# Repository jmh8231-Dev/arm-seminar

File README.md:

# ARM Seminar Board — Training Kit Rev 2.0

> **MCU:** STM32F405VGT6 (Cortex‑M4)  

ARM Seminar Board (Rev 2.0)는 GPIO부터 SDIO, FMC‑SDRAM, QSPI, CAN, USB, Wi‑Fi(IoT), RTC까지  
현업에서 자주 쓰는 주변장치를 **한 장의 보드에서 단계적으로 실습**할 수 있도록 구성한 트레이닝 키트입니다.

---

## Contents
- [Hardware overview](#hardware-overview)
- [Images](#images)
- [Getting started](#getting-started)
- [Peripheral quick map](#peripheral-quick-map)
- [Curriculum (16 + n)](#curriculum-16--n)
- [Revision notes](#revision-notes)
- [Repository layout](#repository-layout)
- [License](#license)

---

## Hardware overview

> 아래 구성은 **블록 다이어그램 / 보드 실크 라벨 기준**으로 정리했습니다.

### Core / Storage

| Category | Item | Interface / Notes |
|---|---|---|
| MCU | STM32F405VGT6 | Cortex‑M4 |
| microSD | microSD socket | **SDIO (4‑bit)** |

### USB / Debug

| Item | Notes |
|---|---|
| USB Type‑C | 5V 전원 / PC 연결 |
| USB OTG FS | USB 2.0 Full‑Speed |
| UART‑to‑USB | FT232RL 기반 로그/콘솔 |

### Display

| Item | Notes |
|---|---|
| 2004 CLCD | 캐릭터 LCD |

### Connectivity

| Item | Interface / Notes |
|---|---|
| Wi‑Fi module | ESP‑12F (**UART**) |
| CAN | CAN Tx/Rx + 커넥터 |

### Sensors / Inputs / Actuators

| Item | Notes |
|---|---|
| RTC | DS3231 + CR2032 |
| EEPROM | I2C |
| Temp sensor | AS6221 |
| Analog inputs | CDS Cell, 가변저항(ADC 실습) |
| User I/O | LEDs, Buttons, GPIO/EXTI 스위치 |
| Actuator | SG90 Servo(PWM), Passive Buzzer |

---

## Images

### Block diagram

### Board photos

---

## Getting started

### Power
- **USB Type‑C**로 5V 전원 공급 (PC/어댑터 모두 가능)
- RTC는 **CR2032** 장착 시 전원 분리 후에도 시간 유지

### Flash / Debug
- **ST‑Link/V2 헤더**로 다운로드/디버깅
- 또는 UART‑to‑USB(FT232RL)로 시리얼 콘솔/로그 출력

### Recommended dev environment
- STM32CubeIDE, STM32CubeMX (권장)
- (선택) STM32CubeProgrammer, Logic Analyzer, CAN‑USB, USB‑TTL

---

## Peripheral quick map

교육 진행 시 “오늘 실습 대상”을 빠르게 체크할 수 있도록 묶었습니다.

- **GPIO / EXTI:** 버튼/스위치, LED  
- **ADC / DMA:** CDS Cell, 가변저항  
- **Timer / PWM:** Servo(SG90), Buzzer  
- **UART:** PC 디버그 콘솔, Wi‑Fi(ESP‑12F)  
- **I2C:** EEPROM, AS6221, DS3231(RTC)  
- **SPI:** 확장(예: VS1003 등)  
- **SDIO / FATFS:** microSD 파일 시스템  
- **CAN:** 보드 커넥터  

---

## Curriculum (10 + 6)

세미나는 총 **10 + 6회차**로 구성되며, 초급 → 고급으로 난이도가 점진적으로 상승하도록 설계했습니다.

- CubeIDE / GPIO / EXTI
- UART(폴링/인터럽트), printf 디버그
- CLCD 출력, ADC/DMA, Timer
- PWM/서보/버저 제어
- USB (예: Mass Storage)
- SDIO + FATFS, SPI, I2C, CAN
- FreeRTOS

---

## Revision notes

Rev 1.0 대비 주요 변경 사항 (요약)

- RTC 배터리 홀더 위치 변경(Back side)
- USB Type‑C 라인 다이오드 삭제
- UART 기반 업로드/연동 편의 개선
- 실크스크린 영역/사이즈 조정, 날짜/버전 업데이트

---

## License

**All Rights Reserved.**

본 저장소의 회로/PCB/문서/이미지/콘텐츠는 저작권자의 사전 서면 허가 없이  
**복제, 배포, 상업적 이용, 2차 저작물 제작**을 금지합니다.

교육/연구 목적의 검토가 필요하다면 저작권자에게 사용 허가를 요청해 주세요.  
자세한 내용은 `LICENSE`를 참조합니다.

© 2025 MyungHoon Jung. All rights reserved.

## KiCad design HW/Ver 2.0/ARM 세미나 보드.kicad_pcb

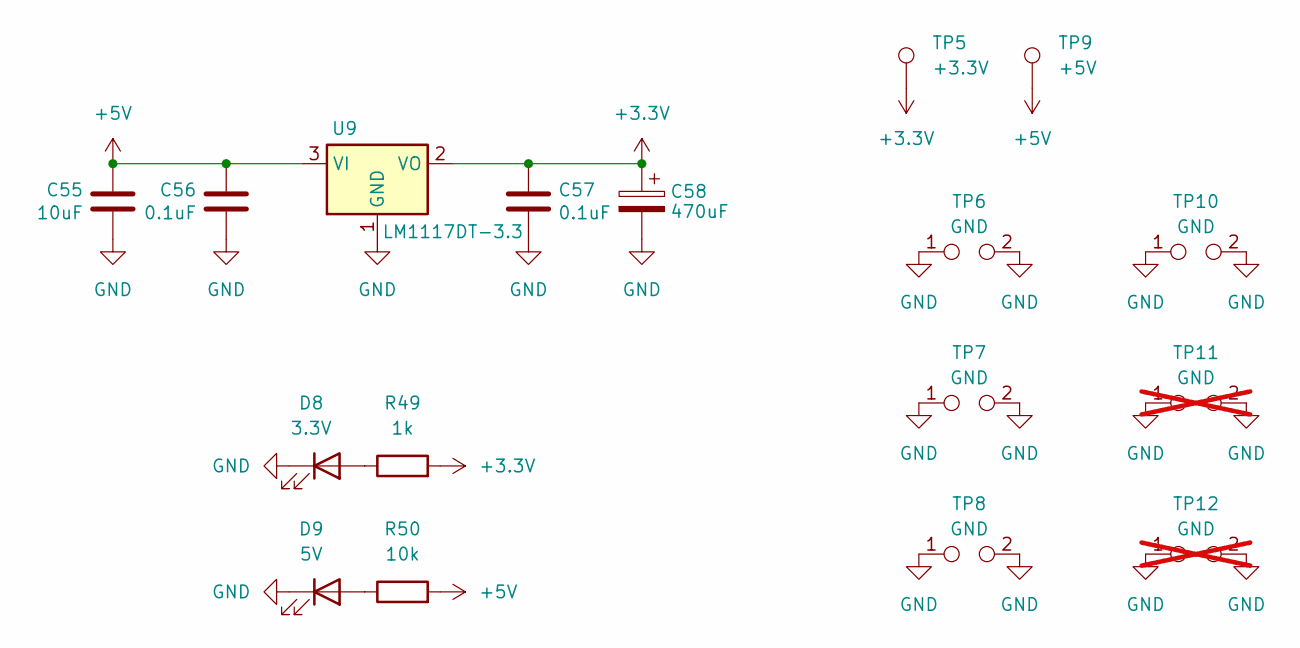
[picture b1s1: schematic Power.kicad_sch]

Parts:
C55: 10uF; C_1206_3216Metric
C56, C57: 0.1uF; C_0805_2012Metric
C58: 470uF; MVG25WV470M
D8: 3.3V; LED_0805_2012Metric
D9: 5V; LED_0805_2012Metric
R49: 1k; R_0805_2012Metric
R50: 10k; R_0805_2012Metric
TP5: +3.3V; TestPoint_Pad_D1.5mm
TP6, TP7, TP8, TP10: GND; TestPoint_2Pads_Pitch5.08mm_Drill1.3mm
TP9: +5V; TestPoint_Pad_D1.5mm
TP11, TP12: GND; TestPoint_2Pads_Pitch5.08mm_Drill1.3mm; not fitted
U9: LM1117DT-3.3; TO-252-3_TabPin2

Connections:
+3.3V: C57.2, C58.1, R49.2, TP5.1, U9.2 (VO); also elsewhere on the board
+5V: C55.2, C56.2, R50.2, TP9.1, U9.3 (VI); also elsewhere on the board
GND: C55.1, C56.1, C57.1, C58.2, D8.1 (K), D9.1 (K), TP6.1, TP6.2, TP7.1, TP7.2, TP8.1, TP8.2, TP10.1, TP10.2, TP11.1, TP11.2, TP12.1, TP12.2, U9.1 (GND); also elsewhere on the board
unnamed: D8.2 (A), R49.1
unnamed: D9.2 (A), R50.1

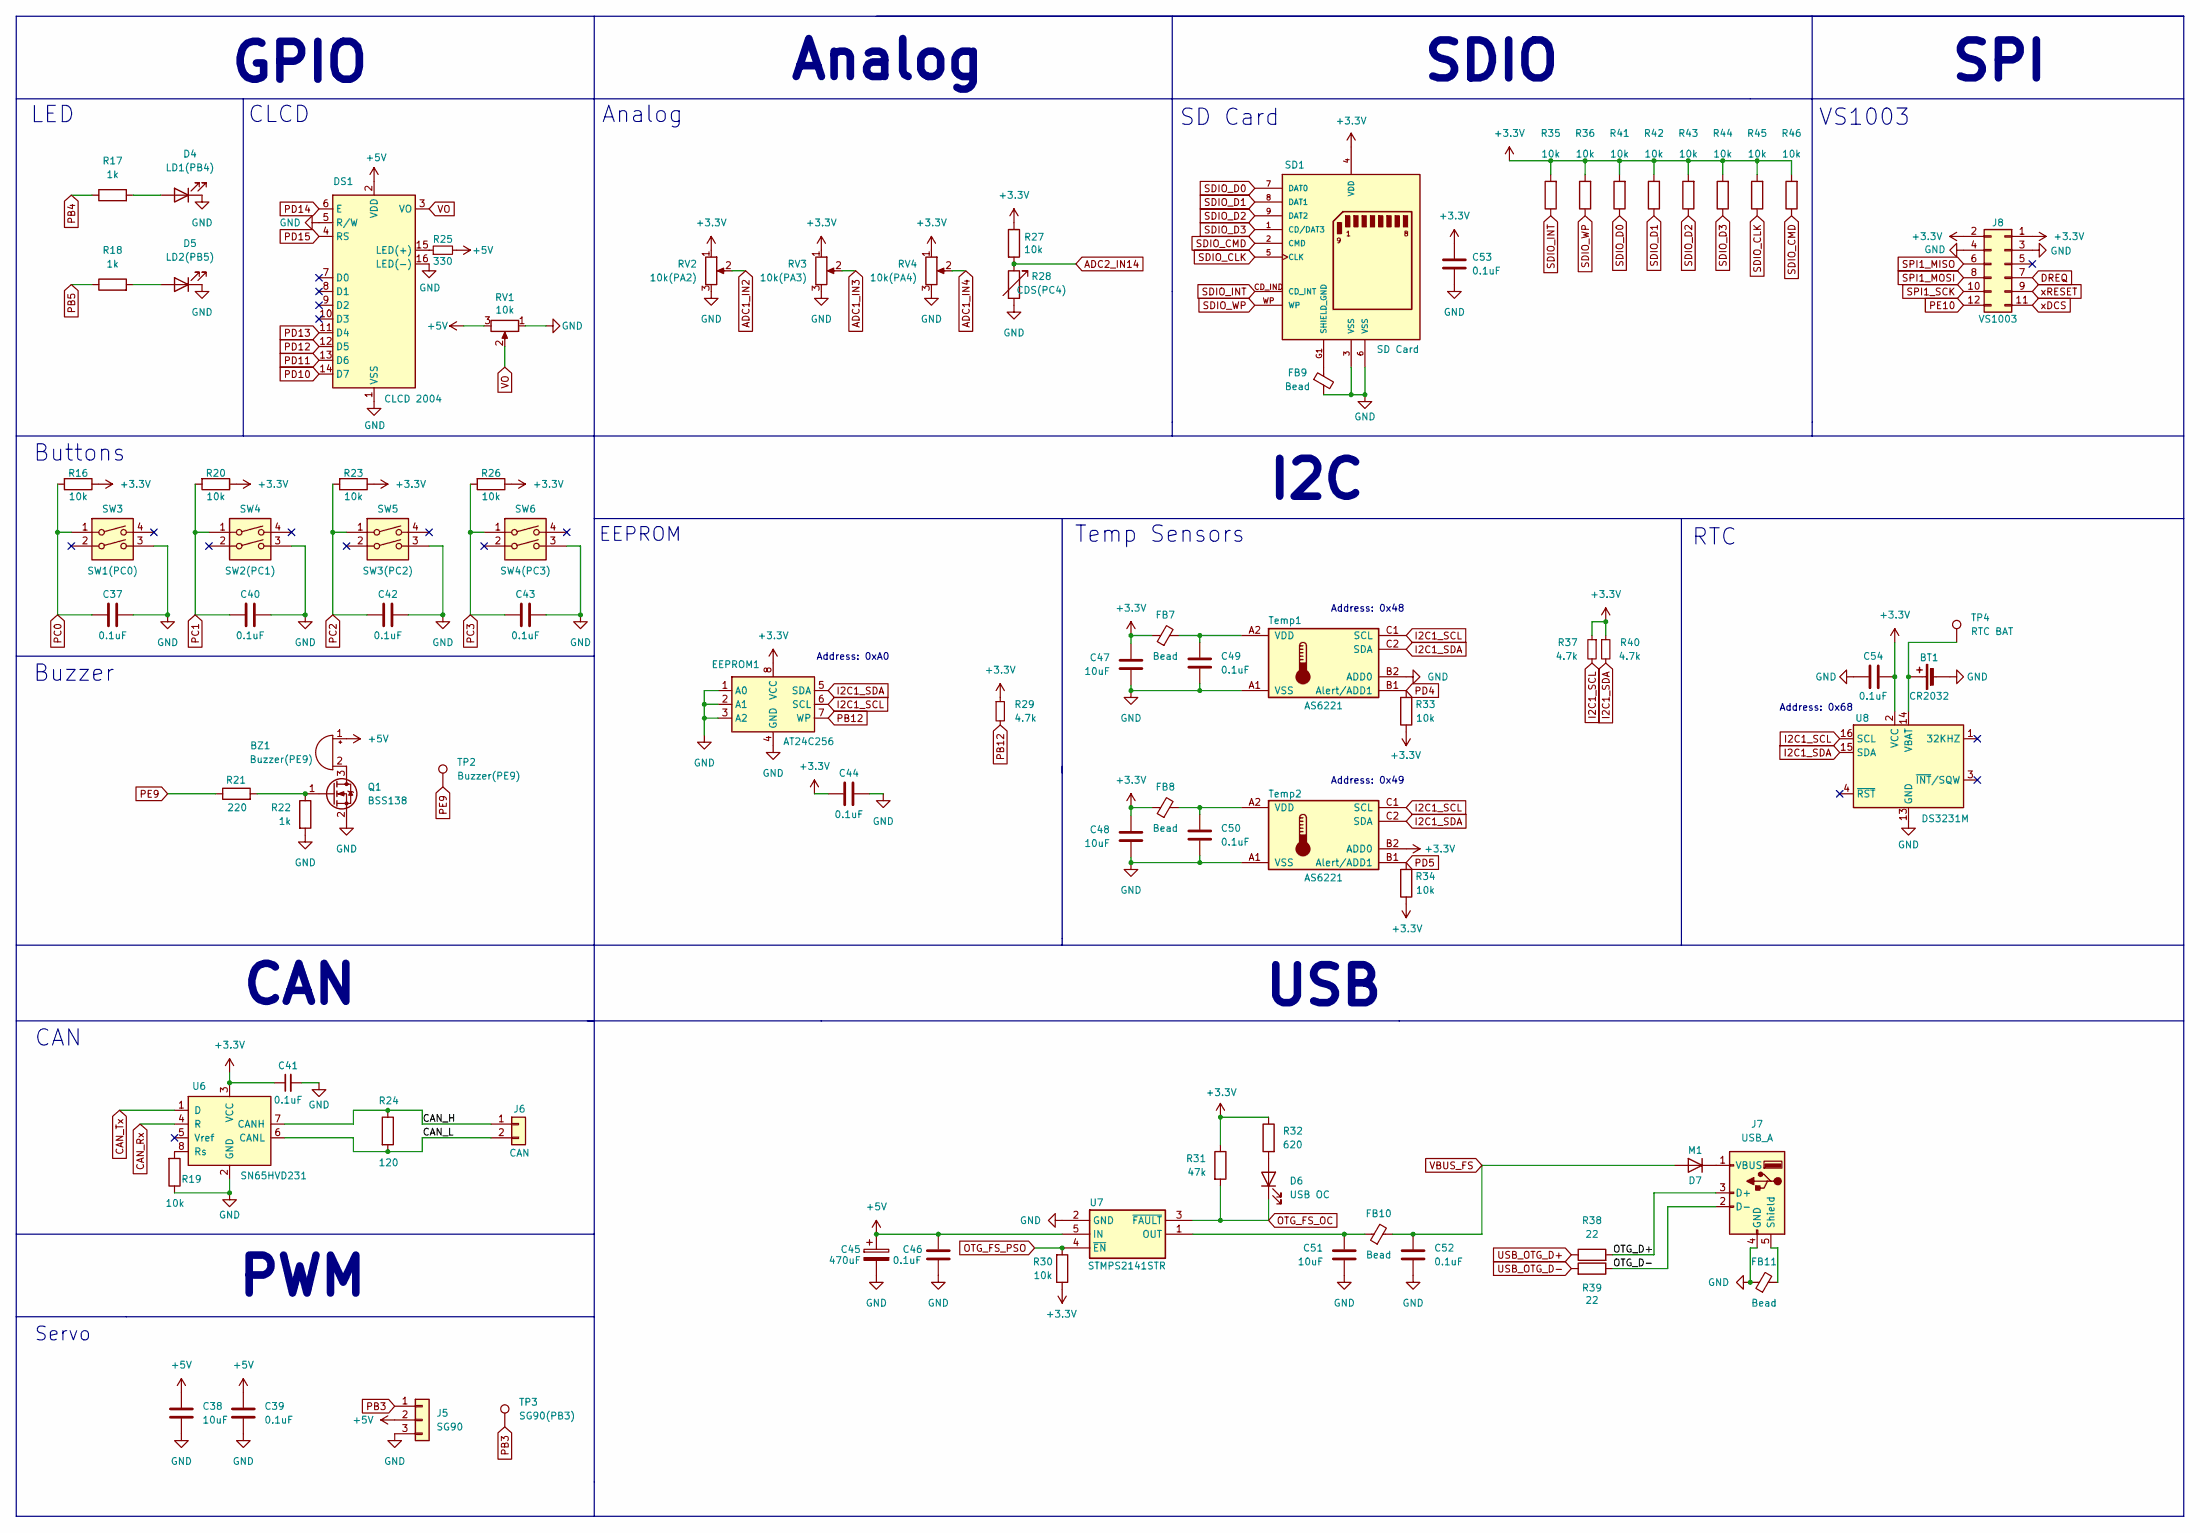
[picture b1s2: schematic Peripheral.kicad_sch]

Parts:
BT1: CR2032; BAT-HLD-001
BZ1: Buzzer(PE9); Buzzer_12x9.5RM7.6
C37, C39, C40, C41, C42, C43, C44, C46, C49, C50, C52, C53, C54: 0.1uF; C_0805_2012Metric
C38, C47, C48, C51: 10uF; C_1206_3216Metric
C45: 470uF; MVG25WV470M
D4: LD1(PB4); LED_0805_2012Metric
D5: LD2(PB5); LED_0805_2012Metric
D6: USB OC; LED_0805_2012Metric
D7: M1; D_SMA
DS1: CLCD 2004; LCD-20x4
EEPROM1: AT24C256; SOIC-8_3.9x4.9mm_P1.27mm
FB7, FB8, FB9, FB10, FB11: Bead; L_0805_2012Metric
J5: SG90; PinHeader_1x03_P2.54mm_Vertical
J6: CAN; PinHeader_1x02_P2.54mm_Vertical
J7: USB_A; USB_A_Connfly_DS1095
J8: VS1003; PinSocket_2x06_P2.54mm_Vertical
Q1: BSS138; SOT-23
R16, R19, R20, R23, R26, R27, R30, R33, R34, R35, R36, R41, R42, R43, R44, R45, R46: 10k; R_0805_2012Metric
R17, R18, R22: 1k; R_0805_2012Metric
R21: 220; R_0805_2012Metric
R24: 120; R_0805_2012Metric
R25: 330; R_0805_2012Metric
R28: CDS(PC4); R_LDR_5.0x4.1mm_P3mm_Vertical
R29, R37, R40: 4.7k; R_0805_2012Metric
R31: 47k; R_0805_2012Metric
R32: 620; R_0805_2012Metric
R38, R39: 22; R_0805_2012Metric
RV1: 10k; 3362P-103LF
RV2: 10k(PA2); RV09H20SQ-B10K
RV3: 10k(PA3); RV09H20SQ-B10K
RV4: 10k(PA4); RV09H20SQ-B10K
SD1: SD Card; AMPHENOL_GSD090012SEU; PARTREV E
SW3: SW1(PC0); SW_SMD_IT-1107
SW4: SW2(PC1); SW_SMD_IT-1107
SW5: SW3(PC2); SW_SMD_IT-1107
SW6: SW4(PC3); SW_SMD_IT-1107
TP2: Buzzer(PE9); TestPoint_Pad_D1.5mm
TP3: SG90(PB3); TestPoint_Pad_D1.5mm
TP4: RTC BAT; TestPoint_Pad_D1.5mm
Temp1, Temp2: AS6221; WLCSP-6_1.4x1.0mm_P0.4mm
U6: SN65HVD231; SOIC-8_3.9x4.9mm_P1.27mm
U7: STMPS2141STR; SOT-23-5
U8: DS3231M; SOIC-16W_7.5x10.3mm_P1.27mm

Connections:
+3.3V: C41.1, C44.1, C47.2, C48.2, C53.1, C54.2, EEPROM1.8 (VCC), FB7.1, FB8.1, J8.1, J8.2, R16.1, R20.1, R23.1, R26.1, R27.1, R29.1, R30.1, R31.1, R32.1, R33.1, R34.1, R35.2, R36.2, R37.1, R40.1, R41.2, R42.2, R43.2, R44.2, R45.2, R46.2, RV2.1, RV3.1, RV4.1, SD1.4 (VDD), Temp2.B2 (ADD0), U6.3 (VCC), U8.2 (VCC); also elsewhere on the board
+5V: BZ1.1 (+), C38.1, C39.1, C45.1, C46.1, DS1.2 (VDD), J5.2, R25.2, RV1.3, U7.5 (IN); also elsewhere on the board
/Peripheral/CAN_H: J6.1, R24.1, U6.7 (CANH)
/Peripheral/CAN_L: J6.2, R24.2, U6.6 (CANL)
/Peripheral/OTG_D+: J7.3 (D+), R38.2
/Peripheral/OTG_D-: J7.2 (D-), R39.1
ADC1_IN2: RV2.2; also elsewhere on the board
ADC1_IN3: RV3.2; also elsewhere on the board
ADC1_IN4: RV4.2; also elsewhere on the board
ADC2_IN14: R27.2, R28.1; also elsewhere on the board
CAN_Rx: U6.4 (R); also elsewhere on the board
CAN_Tx: U6.1 (D); also elsewhere on the board
DREQ: J8.7; also elsewhere on the board
GND: BT1.2 (-), C37.2, C38.2, C39.2, C40.2, C41.2, C42.2, C43.2, C44.2, C45.2, C46.2, C47.1, C48.1, C49.2, C50.2, C51.1, C52.2, C53.2, C54.1, D4.1 (K), D5.1 (K), DS1.1 (VSS), DS1.5 (R/W), DS1.16 (LED(-)), EEPROM1.1 (A0), EEPROM1.2 (A1), EEPROM1.3 (A2), EEPROM1.4 (GND), FB9.2, FB11.1, J5.3, J7.4 (GND), J8.3, J8.4, Q1.2 (S), R19.1, R22.2, R28.2, RV1.1, RV2.3, RV3.3, RV4.3, SD1.3 (VSS), SD1.6 (VSS), SW3.3, SW4.3, SW5.3, SW6.3, Temp1.A1 (VSS), Temp1.B2 (ADD0), Temp2.A1 (VSS), U6.2 (GND), U7.2 (GND), U8.5 (GND), U8.6 (GND), U8.7 (GND), U8.8 (GND), U8.9 (GND), U8.10 (GND), U8.11 (GND), U8.12 (GND), U8.13 (GND); also elsewhere on the board
I2C1_SCL: EEPROM1.6 (SCL), R37.2, Temp1.C1 (SCL), Temp2.C1 (SCL), U8.16 (SCL); also elsewhere on the board
I2C1_SDA: EEPROM1.5 (SDA), R40.2, Temp1.C2 (SDA), Temp2.C2 (SDA), U8.15 (SDA); also elsewhere on the board
unnamed: BT1.1 (+), TP4.1, U8.14 (VBAT)
unnamed: BZ1.2 (-), Q1.3 (D)
unnamed: D4.2 (A), R17.2
unnamed: D5.2 (A), R18.2
unnamed: D6.2 (A), R32.2
unnamed: D7.1 (K), J7.1 (VBUS)
unnamed: DS1.15 (LED(+)), R25.1
unnamed: FB11.2, J7.5 (Shield)
unnamed: Q1.1 (G), R21.2, R22.1
unnamed: C49.1, FB7.2, Temp1.A2 (VDD)
unnamed: C50.1, FB8.2, Temp2.A2 (VDD)
unnamed: R19.2, U6.8 (Rs)
unnamed: C51.2, FB10.1, U7.1 (OUT)
OTG_FS_OC: D6.1 (K), R31.2, U7.3 (~FAULT); also elsewhere on the board
OTG_FS_PSO: R30.2, U7.4 (~EN); also elsewhere on the board
PB3: J5.1, TP3.1; also elsewhere on the board
PB4: R17.1; also elsewhere on the board
PB5: R18.1; also elsewhere on the board
PB12: EEPROM1.7 (WP), R29.2; also elsewhere on the board
PC0: C37.1, R16.2, SW3.1; also elsewhere on the board
PC1: C40.1, R20.2, SW4.1; also elsewhere on the board
PC2: C42.1, R23.2, SW5.1; also elsewhere on the board
PC3: C43.1, R26.2, SW6.1; also elsewhere on the board
PD4: R33.2, Temp1.B1 (Alert/ADD1); also elsewhere on the board
PD5: R34.2, Temp2.B1 (Alert/ADD1); also elsewhere on the board
PD10: DS1.14 (D7); also elsewhere on the board
PD11: DS1.13 (D6); also elsewhere on the board
PD12: DS1.12 (D5); also elsewhere on the board
PD13: DS1.11 (D4); also elsewhere on the board
PD14: DS1.6 (E); also elsewhere on the board
PD15: DS1.4 (RS); also elsewhere on the board
PE9: R21.1, TP2.1; also elsewhere on the board
PE10: J8.12; also elsewhere on the board
SDIO_CLK: R45.1, SD1.5 (CLK); also elsewhere on the board
SDIO_CMD: R46.1, SD1.2 (CMD); also elsewhere on the board
SDIO_D0: R41.1, SD1.7 (DAT0); also elsewhere on the board
SDIO_D1: R42.1, SD1.8 (DAT1); also elsewhere on the board
SDIO_D2: R43.1, SD1.9 (DAT2); also elsewhere on the board
SDIO_D3: R44.1, SD1.1 (CD/DAT3); also elsewhere on the board
SDIO_INT: R35.1, SD1.CD_IND (CD_INT); also elsewhere on the board
SDIO_WP: R36.1, SD1.WP; also elsewhere on the board
SHIELD_GND: FB9.1, SD1.G1 (SHIELD_GND), SD1.G2 (SHIELD_GND), SD1.G3 (SHIELD_GND), SD1.G4 (SHIELD_GND)
SPI1_MISO: J8.6; also elsewhere on the board
SPI1_MOSI: J8.8; also elsewhere on the board
SPI1_SCK: J8.10; also elsewhere on the board
USB_OTG_D+: R38.1; also elsewhere on the board
USB_OTG_D-: R39.2; also elsewhere on the board
VBUS_FS: C52.1, D7.2 (A), FB10.2; also elsewhere on the board
VO: DS1.3 (VO), RV1.2
xDCS: J8.11; also elsewhere on the board
xRESET: J8.9; also elsewhere on the board

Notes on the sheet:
Address: 0x48
CLCD
Analog
Buttons
Buzzer
Servo
VS1003
Address: 0x68
RTC
EEPROM
LED
CAN
Address: 0xA0
SPI
I2C
Temp Sensors
USB
SD Card
PWM
GPIO
SDIO
Address: 0x49

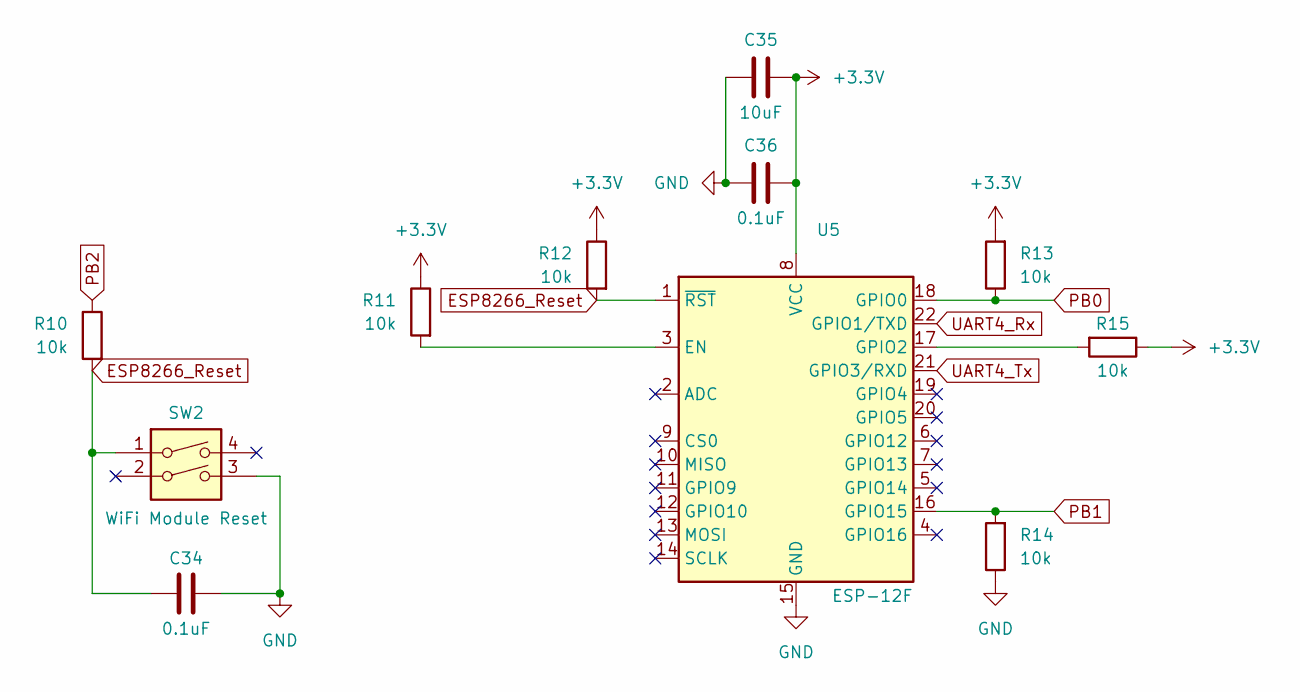
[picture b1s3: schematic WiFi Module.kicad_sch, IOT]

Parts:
C34, C36: 0.1uF; C_0805_2012Metric
C35: 10uF; C_1206_3216Metric
R10, R11, R12, R13, R14, R15: 10k; R_0805_2012Metric
SW2: WiFi Module Reset; SW_SMD_IT-1107
U5: ESP-12F; ESP-12E

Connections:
+3.3V: C35.2, C36.2, R11.1, R12.1, R13.2, R15.1, U5.8 (VCC); also elsewhere on the board
ESP8266_Reset: C34.1, R10.2, R12.2, SW2.1, U5.1 (~RST)
GND: C34.2, C35.1, C36.1, R14.1, SW2.3, U5.15 (GND); also elsewhere on the board
unnamed: R11.2, U5.3 (EN)
unnamed: R15.2, U5.17 (GPIO2)
PB0: R13.1, U5.18 (GPIO0); also elsewhere on the board
PB1: R14.2, U5.16 (GPIO15); also elsewhere on the board
PB2: R10.1; also elsewhere on the board
UART4_Rx: U5.22 (GPIO1/TXD); also elsewhere on the board
UART4_Tx: U5.21 (GPIO3/RXD); also elsewhere on the board

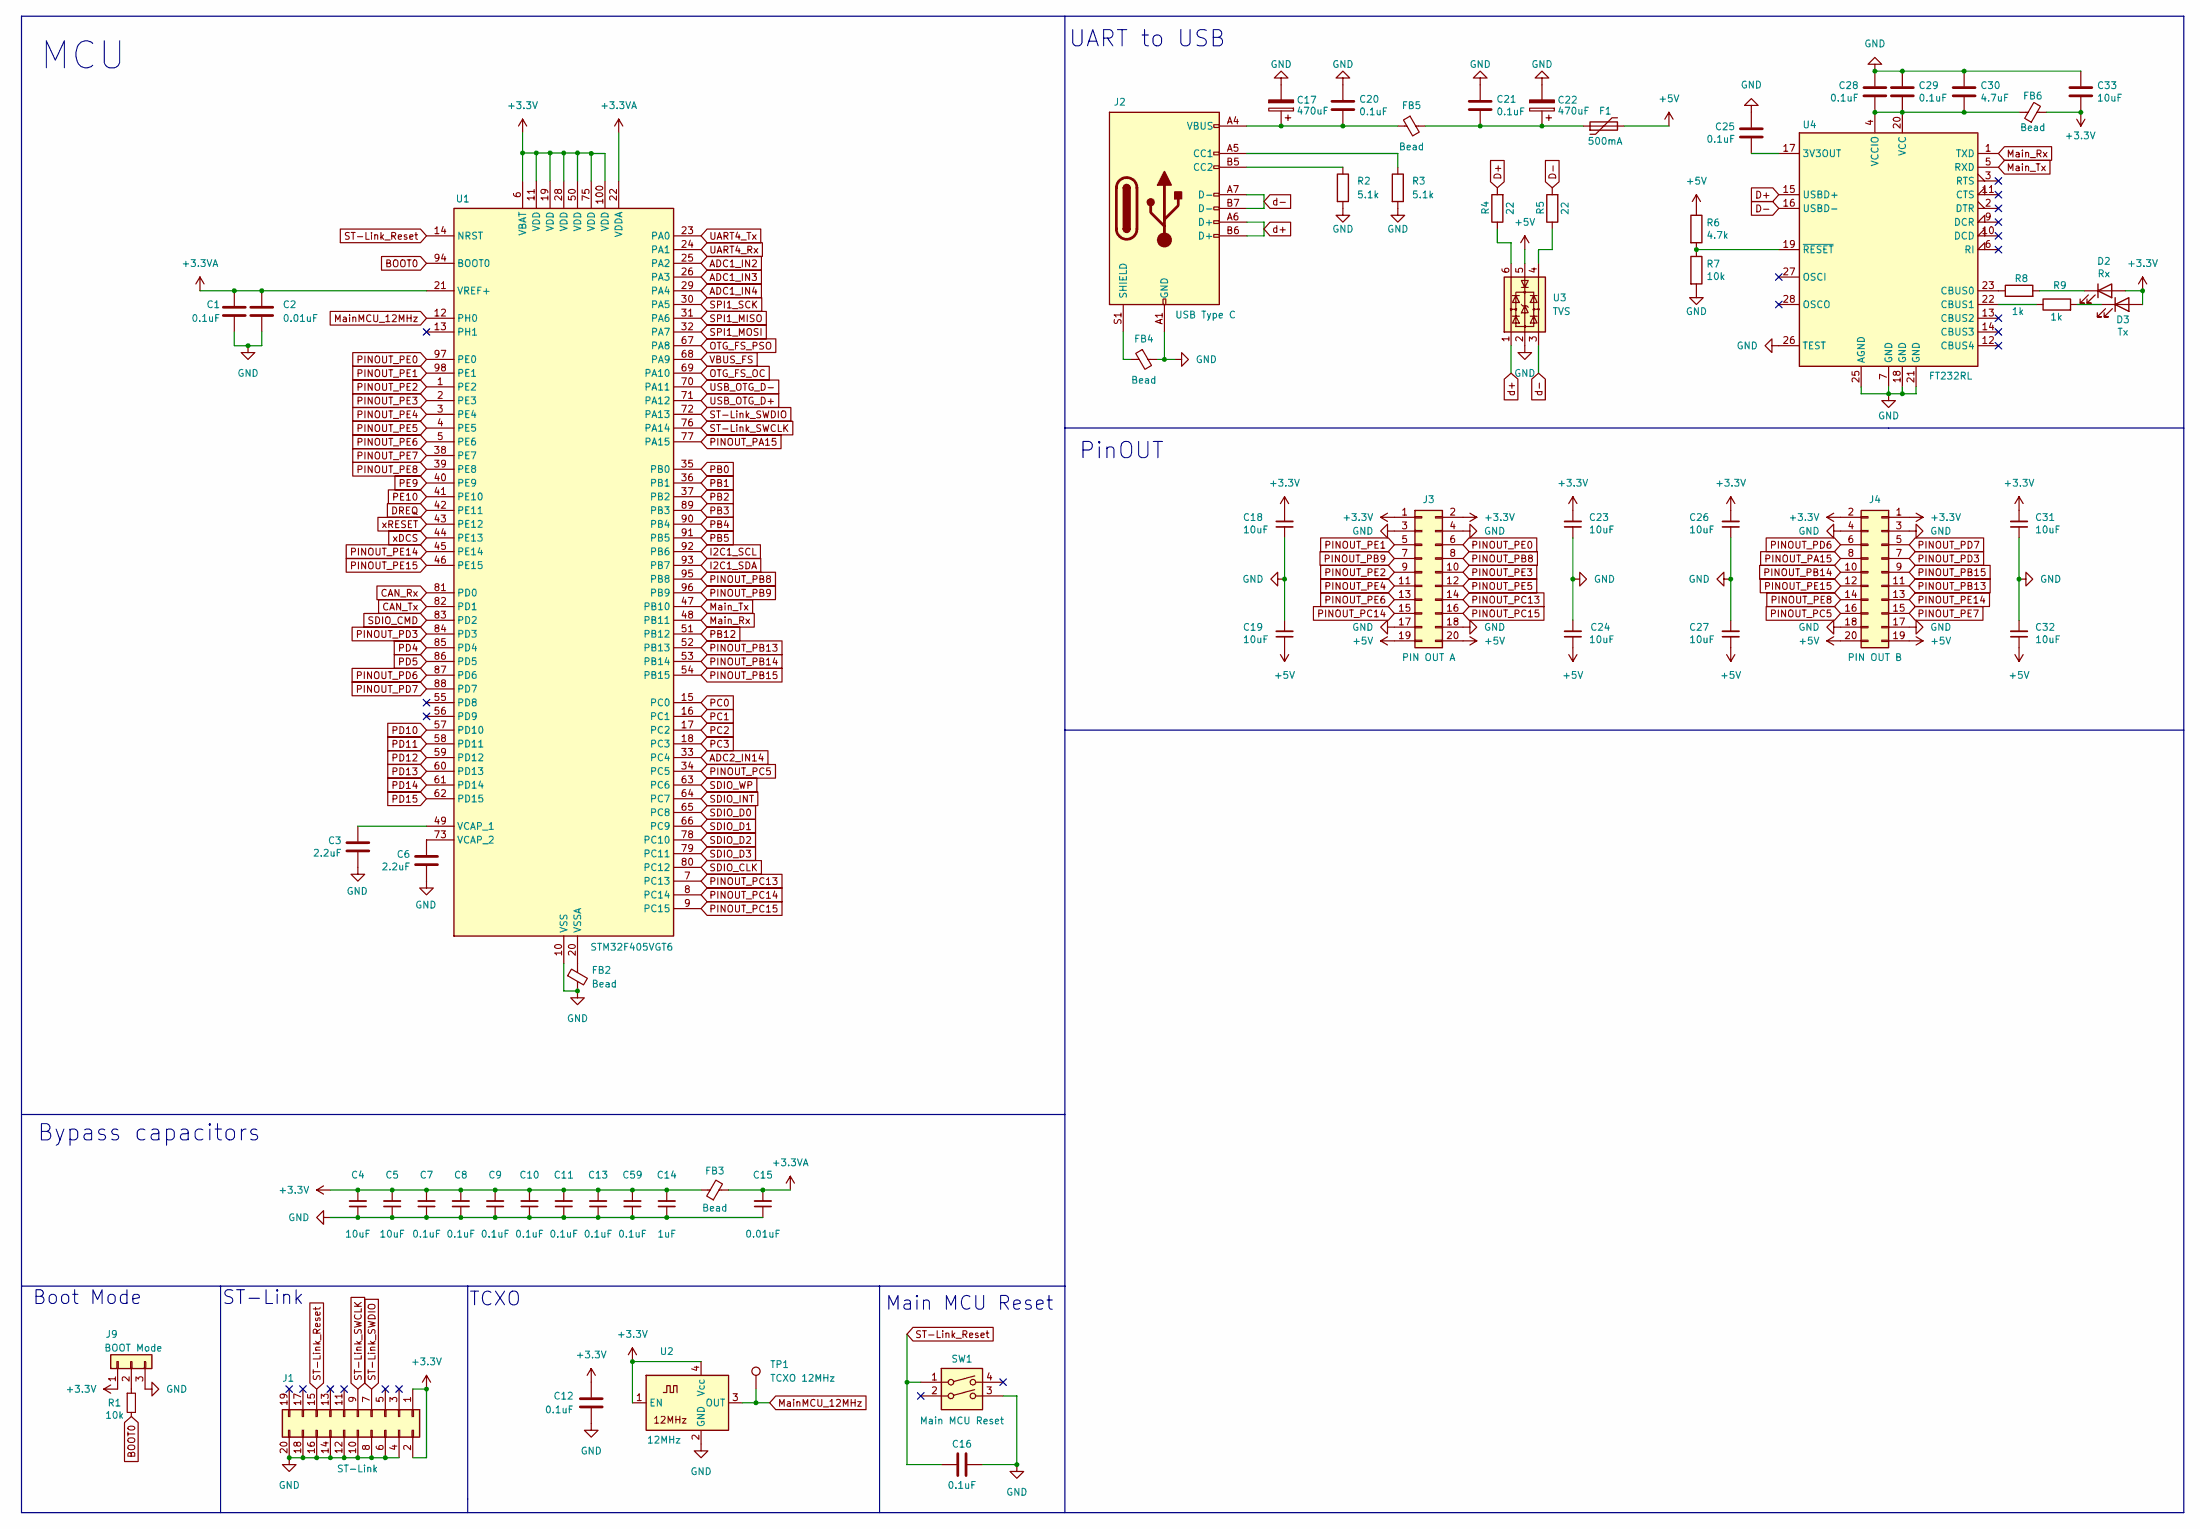
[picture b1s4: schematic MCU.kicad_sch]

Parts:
C1, C7, C8, C9, C10, C11, C12, C13, C16, C20, C21, C25, C28, C29, C59: 0.1uF; C_0805_2012Metric
C2, C15: 0.01uF; C_0805_2012Metric
C3, C6: 2.2uF; C_0805_2012Metric
C4, C5, C18, C19, C23, C24, C26, C27, C31, C32, C33: 10uF; C_1206_3216Metric
C14: 1uF; C_0805_2012Metric
C17, C22: 470uF; MVG25WV470M
C30: 4.7uF; C_0805_2012Metric
D2: Rx; LED_0805_2012Metric
D3: Tx; LED_0805_2012Metric
F1: 500mA; L_1210_3225Metric
FB2, FB3, FB4, FB5, FB6: Bead; L_0805_2012Metric
J1: ST-Link; IDC-Header_2x10_P2.54mm_Vertical
J2: USB Type C; USB_C_Receptacle_HRO_TYPE-C-31-M-12
J3: PIN OUT A; PinHeader_2x10_P2.54mm_Vertical
J4: PIN OUT B; PinHeader_2x10_P2.54mm_Vertical
J9: BOOT Mode; PinHeader_1x03_P2.54mm_Vertical
R1, R7: 10k; R_0805_2012Metric
R2, R3: 5.1k; R_0805_2012Metric
R4, R5: 22; R_0805_2012Metric
R6: 4.7k; R_0805_2012Metric
R8, R9: 1k; R_0805_2012Metric
SW1: Main MCU Reset; SW_SMD_IT-1107
TP1: TCXO 12MHz; TestPoint_Pad_D1.5mm
U1: STM32F405VGT6; LQFP-100_14x14mm_P0.5mm
U2: 12MHz; ECS-TXO-2016
U3: TVS; SOT-23-6
U4: FT232RL; SSOP-28_5.3x10.2mm_P0.65mm

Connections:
+3.3V: C4.2, C5.2, C7.2, C8.2, C9.2, C10.2, C11.2, C12.1, C13.2, C14.2, C18.2, C23.2, C26.2, C31.2, C33.1, C59.2, D2.2 (A), D3.2 (A), FB3.1, FB6.2, J1.1, J1.2, J3.1, J3.2, J4.1, J4.2, J9.1, U1.6 (VBAT), U1.11 (VDD), U1.19 (VDD), U1.28 (VDD), U1.50 (VDD), U1.75 (VDD), U1.100 (VDD), U2.1 (EN), U2.4 (Vcc); also elsewhere on the board
+3.3VA: C1.2, C2.2, C15.2, FB3.2, U1.21 (VREF+), U1.22 (VDDA)
+5V: C19.1, C24.1, C27.1, C32.1, F1.2, J3.19, J3.20, J4.19, J4.20, R6.1, U3.5; also elsewhere on the board
ADC1_IN2: U1.25 (PA2); also elsewhere on the board
ADC1_IN3: U1.26 (PA3); also elsewhere on the board
ADC1_IN4: U1.29 (PA4); also elsewhere on the board
ADC2_IN14: U1.33 (PC4); also elsewhere on the board
BOOT0: R1.2, U1.94 (BOOT0)
CAN_Rx: U1.81 (PD0); also elsewhere on the board
CAN_Tx: U1.82 (PD1); also elsewhere on the board
D+: R4.2, U4.15 (USBD+)
D-: R5.2, U4.16 (USBD-)
DREQ: U1.42 (PE11); also elsewhere on the board
GND: C1.1, C2.1, C3.2, C4.1, C5.1, C6.2, C7.1, C8.1, C9.1, C10.1, C11.1, C12.2, C13.1, C14.1, C15.1, C16.2, C17.2, C18.1, C19.2, C20.2, C21.2, C22.2, C23.1, C24.2, C25.2, C26.1, C27.2, C28.2, C29.2, C30.2, C31.1, C32.2, C33.2, C59.1, FB2.2, FB4.2, J1.4, J1.6, J1.8, J1.10, J1.12, J1.14, J1.16, J1.18, J1.20, J2.A1 (GND), J2.A12 (GND), J2.B1 (GND), J2.B12 (GND), J3.3, J3.4, J3.17, J3.18, J4.3, J4.4, J4.17, J4.18, J9.3, R2.2, R3.2, R7.2, SW1.3, U1.10 (VSS), U1.27 (VSS), U1.74 (VSS), U1.99 (VSS), U2.2 (GND), U3.2, U4.7 (GND), U4.18 (GND), U4.21 (GND), U4.25 (AGND), U4.26 (TEST); also elsewhere on the board
I2C1_SCL: U1.92 (PB6); also elsewhere on the board
I2C1_SDA: U1.93 (PB7); also elsewhere on the board
MainMCU_12MHz: TP1.1, U1.12 (PH0), U2.3 (OUT)
Main_Rx: U1.48 (PB11), U4.1 (TXD)
Main_Tx: U1.47 (PB10), U4.5 (RXD)
unnamed: C17.1, C20.1, FB5.1, J2.A4 (VBUS), J2.A9 (VBUS), J2.B4 (VBUS), J2.B9 (VBUS)
unnamed: C21.1, C22.1, F1.1, FB5.2
unnamed: D2.1 (K), R8.2
unnamed: D3.1 (K), R9.2
unnamed: J2.A5 (CC1), R3.1
unnamed: J2.B5 (CC2), R2.1
unnamed: FB4.1, J2.S1 (SHIELD)
unnamed: J9.2, R1.1
unnamed: R4.1, U3.6
unnamed: R5.1, U3.4
unnamed: C3.1, U1.49 (VCAP_1)
unnamed: C6.1, U1.73 (VCAP_2)
unnamed: FB2.1, U1.20 (VSSA)
unnamed: C25.1, U4.17 (3V3OUT)
unnamed: R8.1, U4.23 (CBUS0)
unnamed: R9.1, U4.22 (CBUS1)
unnamed: C28.1, C29.1, C30.1, FB6.1, U4.4 (VCCIO), U4.20 (VCC)
unnamed: R6.2, R7.1, U4.19 (~RESET)
OTG_FS_OC: U1.69 (PA10); also elsewhere on the board
OTG_FS_PSO: U1.67 (PA8); also elsewhere on the board
PB0: U1.35 (PB0); also elsewhere on the board
PB1: U1.36 (PB1); also elsewhere on the board
PB2: U1.37 (PB2); also elsewhere on the board
PB3: U1.89 (PB3); also elsewhere on the board
PB4: U1.90 (PB4); also elsewhere on the board
PB5: U1.91 (PB5); also elsewhere on the board
PB12: U1.51 (PB12); also elsewhere on the board
PC0: U1.15 (PC0); also elsewhere on the board
PC1: U1.16 (PC1); also elsewhere on the board
PC2: U1.17 (PC2); also elsewhere on the board
PC3: U1.18 (PC3); also elsewhere on the board
PD4: U1.85 (PD4); also elsewhere on the board
PD5: U1.86 (PD5); also elsewhere on the board
PD10: U1.57 (PD10); also elsewhere on the board
PD11: U1.58 (PD11); also elsewhere on the board
PD12: U1.59 (PD12); also elsewhere on the board
PD13: U1.60 (PD13); also elsewhere on the board
PD14: U1.61 (PD14); also elsewhere on the board
PD15: U1.62 (PD15); also elsewhere on the board
PE9: U1.40 (PE9); also elsewhere on the board
PE10: U1.41 (PE10); also elsewhere on the board
PINOUT_PA15: J4.8, U1.77 (PA15)
PINOUT_PB8: J3.8, U1.95 (PB8)
PINOUT_PB9: J3.7, U1.96 (PB9)
PINOUT_PB13: J4.11, U1.52 (PB13)
PINOUT_PB14: J4.10, U1.53 (PB14)
PINOUT_PB15: J4.9, U1.54 (PB15)
PINOUT_PC5: J4.16, U1.34 (PC5)
PINOUT_PC13: J3.14, U1.7 (PC13)
PINOUT_PC14: J3.15, U1.8 (PC14)
PINOUT_PC15: J3.16, U1.9 (PC15)
PINOUT_PD3: J4.7, U1.84 (PD3)
PINOUT_PD6: J4.6, U1.87 (PD6)
PINOUT_PD7: J4.5, U1.88 (PD7)
PINOUT_PE0: J3.6, U1.97 (PE0)
PINOUT_PE1: J3.5, U1.98 (PE1)
PINOUT_PE2: J3.9, U1.1 (PE2)
PINOUT_PE3: J3.10, U1.2 (PE3)
PINOUT_PE4: J3.11, U1.3 (PE4)
PINOUT_PE5: J3.12, U1.4 (PE5)
PINOUT_PE6: J3.13, U1.5 (PE6)
PINOUT_PE7: J4.15, U1.38 (PE7)
PINOUT_PE8: J4.14, U1.39 (PE8)
PINOUT_PE14: J4.13, U1.45 (PE14)
PINOUT_PE15: J4.12, U1.46 (PE15)
SDIO_CLK: U1.80 (PC12); also elsewhere on the board
SDIO_CMD: U1.83 (PD2); also elsewhere on the board
SDIO_D0: U1.65 (PC8); also elsewhere on the board
SDIO_D1: U1.66 (PC9); also elsewhere on the board
SDIO_D2: U1.78 (PC10); also elsewhere on the board
SDIO_D3: U1.79 (PC11); also elsewhere on the board
SDIO_INT: U1.64 (PC7); also elsewhere on the board
SDIO_WP: U1.63 (PC6); also elsewhere on the board
SPI1_MISO: U1.31 (PA6); also elsewhere on the board
SPI1_MOSI: U1.32 (PA7); also elsewhere on the board
SPI1_SCK: U1.30 (PA5); also elsewhere on the board
ST-Link_Reset: C16.1, J1.15, SW1.1, U1.14 (NRST)
ST-Link_SWCLK: J1.9, U1.76 (PA14)
ST-Link_SWDIO: J1.7, U1.72 (PA13)
UART4_Rx: U1.24 (PA1); also elsewhere on the board
UART4_Tx: U1.23 (PA0); also elsewhere on the board
USB_OTG_D+: U1.71 (PA12); also elsewhere on the board
USB_OTG_D-: U1.70 (PA11); also elsewhere on the board
VBUS_FS: U1.68 (PA9); also elsewhere on the board
d+: J2.A6 (D+), J2.B6 (D+), U3.1
d-: J2.A7 (D-), J2.B7 (D-), U3.3
xDCS: U1.44 (PE13); also elsewhere on the board
xRESET: U1.43 (PE12); also elsewhere on the board

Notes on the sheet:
UART to USB
Bypass capacitors
TCXO
MCU
Main MCU Reset
Boot Mode
ST-Link
PinOUT
